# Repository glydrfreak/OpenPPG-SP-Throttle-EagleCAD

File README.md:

# OpenPPG-SP-Throttle-EagleCAD
Eagle CAD files for the OpenPPG Single Prop unit

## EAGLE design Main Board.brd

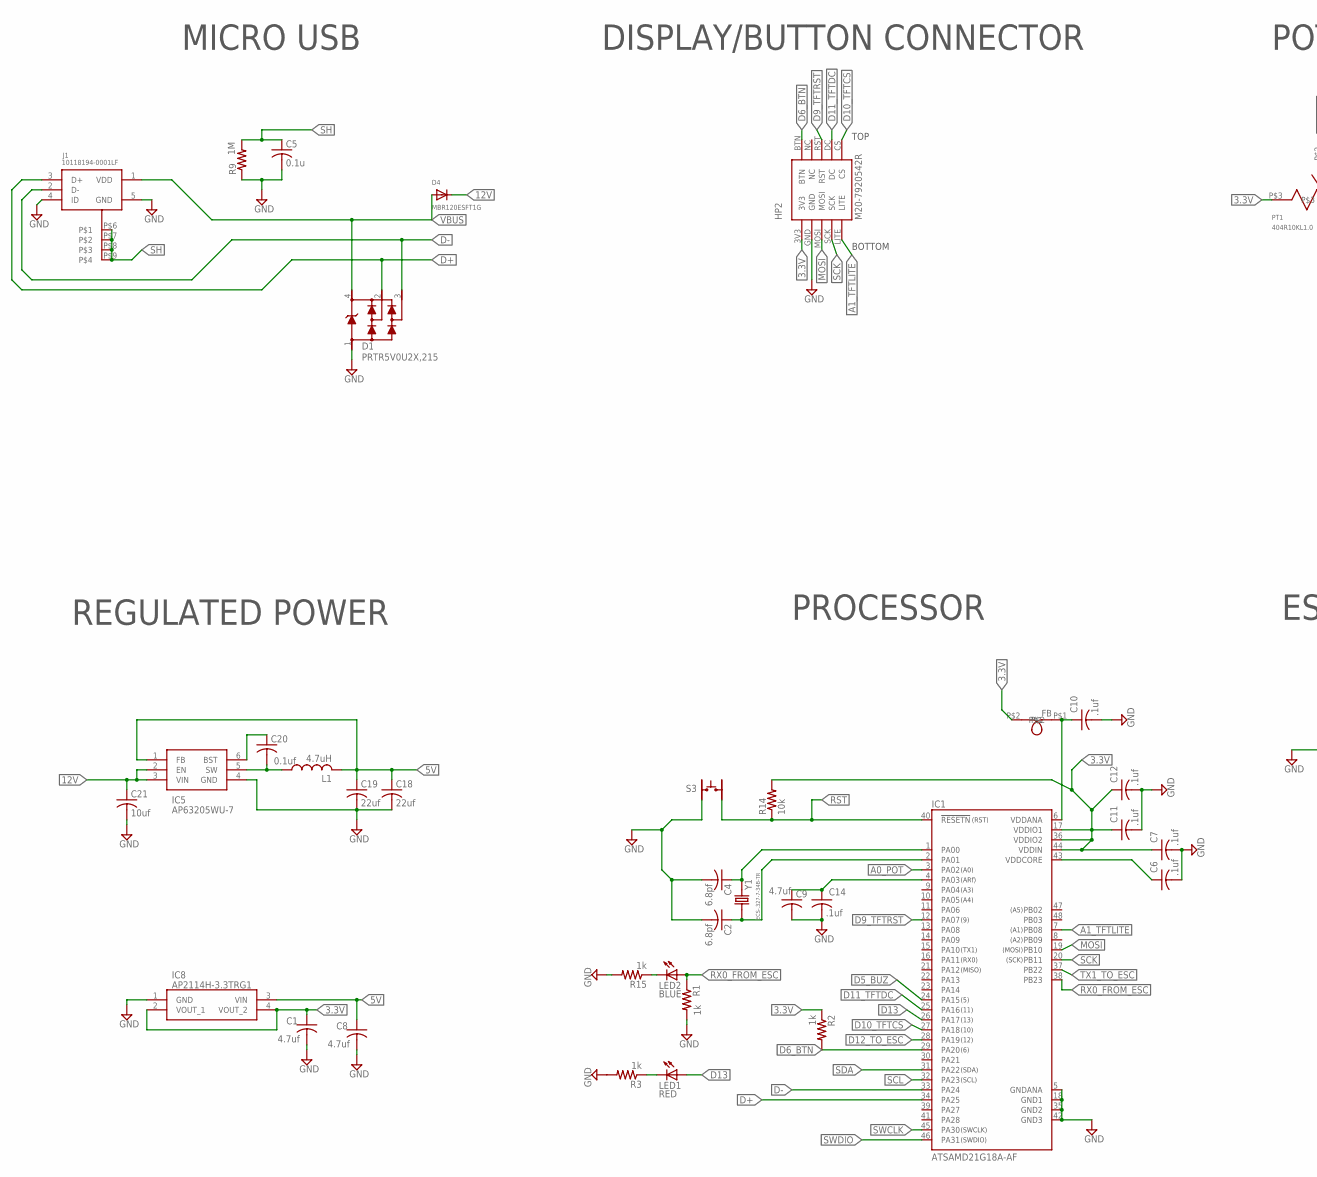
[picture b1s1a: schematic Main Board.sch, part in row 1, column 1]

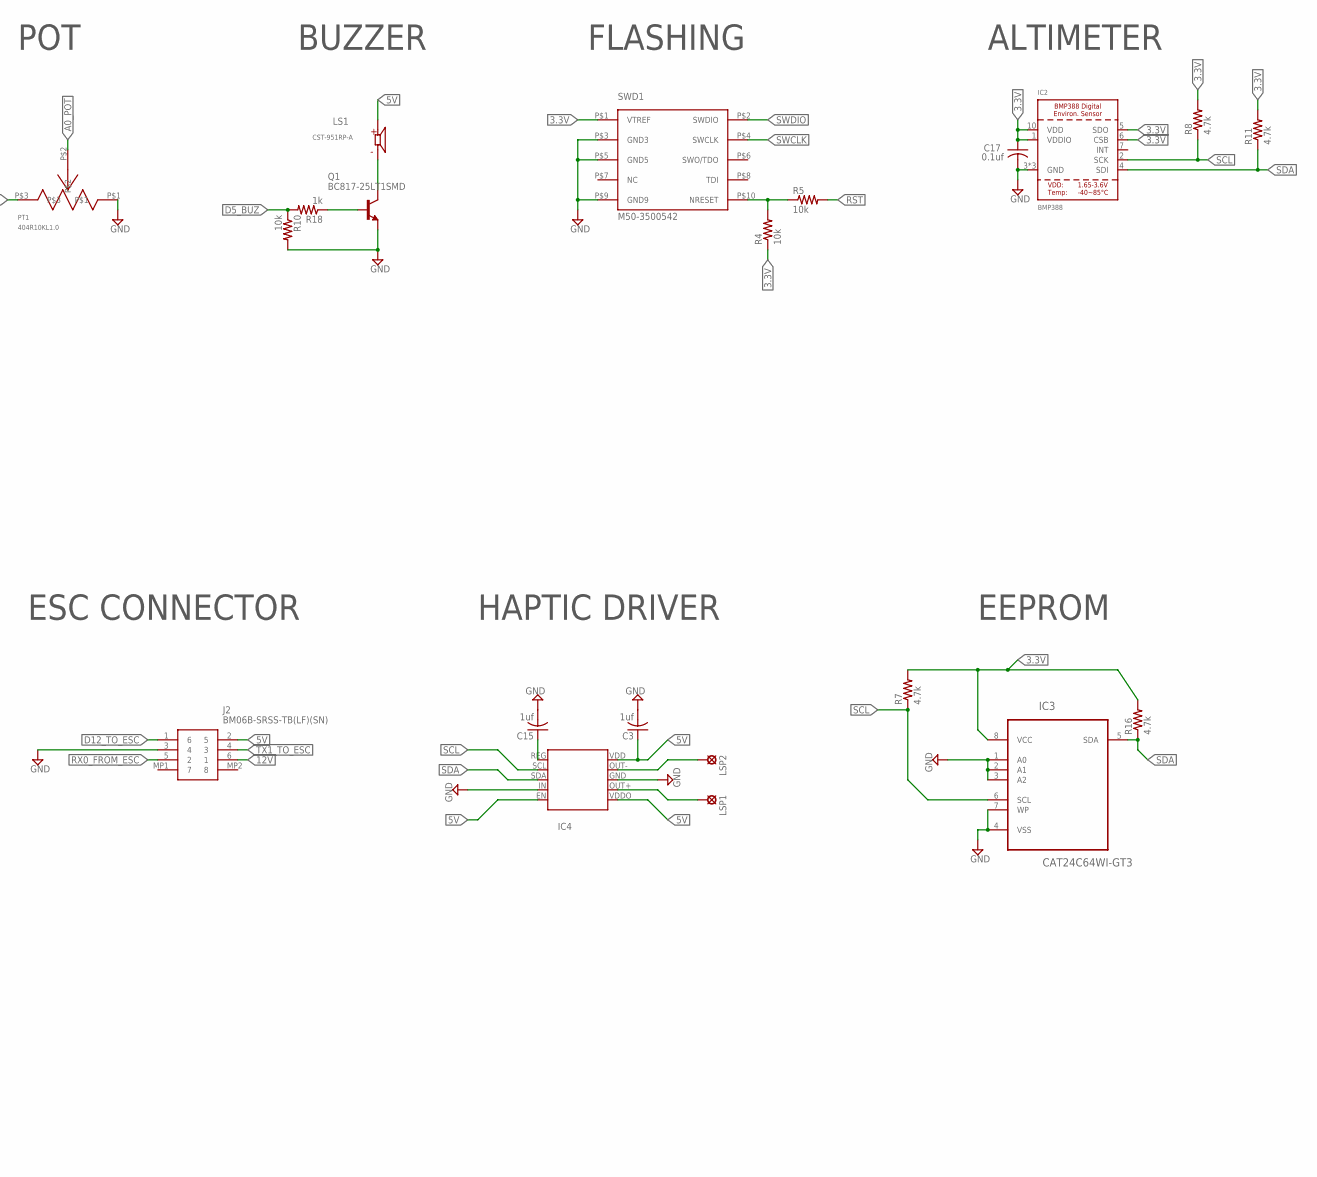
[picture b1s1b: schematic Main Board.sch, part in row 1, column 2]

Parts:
C1, C8, C9: 4.7uf; C0402
C2, C4: 6.8pf; C0402
C3, C15: 1uf; C0402
C5: 0.1u; C0402
C6, C7, C10, C11, C12, C14: .1uf; C0402
C17, C20: 0.1uf; C0402
C18, C19: 22uf; C0603
C21: 10uf; C0805
D1: PRTR5V0U2X,215; SOT143B
D4: MBR120ESFT1G; SOD-123FL
FB: BLM18PG471SN1D; FERRITE_BEAD
HP2: M20-7920542R
IC1: ATSAMD21G18A-AF; QFP50P900X900X120-48N
IC2: BMP388
IC3: CAT24C64WI-GT3; SOIC127P600X175-8N
IC4: DRV2605
IC5: AP63205WU-7; SOT95P280X100-6N
IC8: AP2114H-3.3TRG1; SOT230P700X180-4N
J1: 10118194-0001LF; FRAMATOME_10118194-0001LF
J2: BM06B-SRSS-TB(LF)(SN); BM06BSRSSTBLFSN
L1: 4.7uH; L1812
LED1: RED; CHIP-LED0603
LED2: BLUE; CHIP-LED0603
LS1: CST-951RP-A; CUI_CST-951RP-A
LSP1, LSP2: SE14
PT1: 404R10KL1.0
Q1: BC817-25LT1SMD; SOT23-BEC
R1, R2, R3, R15, R18: 1k; R0402
R4, R5, R10, R14: 10k; R0402
R7, R8, R11, R16: 4.7k; R0402
R9: 1M; R0402
S3: KMR231NG LFS; TATILE_SWITCH
SWD1: M50-3500542
Y1: ECS-.327-7-34B-TR; XTAL_ECS-.327-12.5-34B-C-TR

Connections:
3.3V: C1.1, C7.1, C11.1, C12.1, C17.1, FB.P$2, HP2.3V3, IC1.17 (VDDIO1), IC1.36 (VDDIO2), IC1.44 (VDDIN), IC2.1 (VDDIO), IC2.5 (SDO), IC2.6 (CSB), IC2.10 (VDD), IC3.8 (VCC), IC8.2 (VOUT_1), IC8.4 (VOUT_2), PT1.P$3, R2.1, R4.1, R7.2, R8.2, R11.2, R14.2, R16.2, SWD1.P$1 (VTREF)
5V: C3.1, C8.1, C18.1, C19.1, IC4.EN, IC4.VDD, IC4.VDDO, IC5.1 (FB), IC8.3 (VIN), J2.2 (5), L1.2, LS1.P
12V: C21.1, D4.C, IC5.2 (EN), IC5.3 (VIN), J2.6 (1)
A0_POT: IC1.3 (PA02), PT1.P$2
A1_TFTLITE: HP2.LITE, IC1.7 (PB08)
D5_BUZ: IC1.24 (PA15), R10.1, R18.2
D6_BTN: HP2.BTN, IC1.29 (PA20), R2.2
D9_TFTRST: HP2.RST, IC1.12 (PA07)
D10_TFTCS: HP2.CS, IC1.27 (PA18)
D11_TFTDC: HP2.DC, IC1.25 (PA16)
D12_TO_ESC: IC1.28 (PA19), J2.1 (6)
D13: IC1.26 (PA17), LED1.A
D+: D1.2, IC1.34 (PA25), J1.3 (D+)
D-: D1.3, IC1.33 (PA24), J1.2 (D-)
GND: C1.2, C2.2, C3.2, C4.2, C5.2, C6.2, C7.2, C8.2, C9.2, C10.2, C11.2, C12.2, C14.2, C15.2, C17.2, C18.2, C19.2, C21.2, D1.1, HP2.GND, IC1.5 (GNDANA), IC1.18 (GND1), IC1.35 (GND2), IC1.42 (GND3), IC2.3 (GND), IC2.8 (GND), IC2.9 (GND), IC3.1 (A0), IC3.2 (A1), IC3.3 (A2), IC3.4 (VSS), IC3.7 (WP), IC4.GND, IC4.IN, IC5.4 (GND), IC8.1 (GND), J1.4 (ID), J1.5 (GND), J2.3 (4), PT1.P$1, Q1.E, R1.2, R3.2, R9.1, R10.2, R15.2, S3.P$3, SWD1.P$3 (GND3), SWD1.P$5 (GND5), SWD1.P$9 (GND9)
MOSI: HP2.MOSI, IC1.19 (PB10)
unnamed: C6.1, IC1.43 (VDDCORE)
unnamed: LED1.C, R3.1
unnamed: C4.1, IC1.1 (PA00), Y1.2
unnamed: C2.1, IC1.2 (PA01), Y1.1
unnamed: C10.1, FB.P$1, IC1.6 (VDDANA)
unnamed: R4.2, R5.1, SWD1.P$10 (NRESET)
unnamed: C20.2, IC5.5 (SW), L1.1
unnamed: C20.1, IC5.6 (BST)
unnamed: LED2.C, R15.1
unnamed: IC4.OUT-, LSP2.MP
unnamed: C9.1, C14.1, IC1.4 (PA03)
unnamed: Q1.B, R18.1
unnamed: LS1.M, Q1.C
unnamed: C15.1, IC4.REG
unnamed: IC4.OUT+, LSP1.MP
RST: IC1.40 (!RESETN), R5.2, R14.1, S3.P$4
RX0_FROM_ESC: IC1.38 (PB23), J2.5 (2), LED2.A, R1.1
SCK: HP2.SCK, IC1.20 (PB11)
SCL: IC1.32 (PA23), IC2.2 (SCK), IC3.6 (SCL), IC4.SCL, R7.1, R8.1
SDA: IC1.31 (PA22), IC2.4 (SDI), IC3.5 (SDA), IC4.SDA, R11.1, R16.1
SH: C5.1, J1.P$6, J1.P$7, J1.P$8, J1.P$9, R9.2
SWCLK: IC1.45 (PA30), SWD1.P$4 (SWCLK)
SWDIO: IC1.46 (PA31), SWD1.P$2 (SWDIO)
TX1_TO_ESC: IC1.37 (PB22), J2.4 (3)
VBUS: D1.4, D4.A, J1.1 (VDD)

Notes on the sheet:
POT
BUZZER
DISPLAY/BUTTON CONNECTOR
EEPROM
HAPTIC DRIVER
FLASHING
MICRO USB
PROCESSOR
ESC CONNECTOR
REGULATED POWER
ALTIMETER

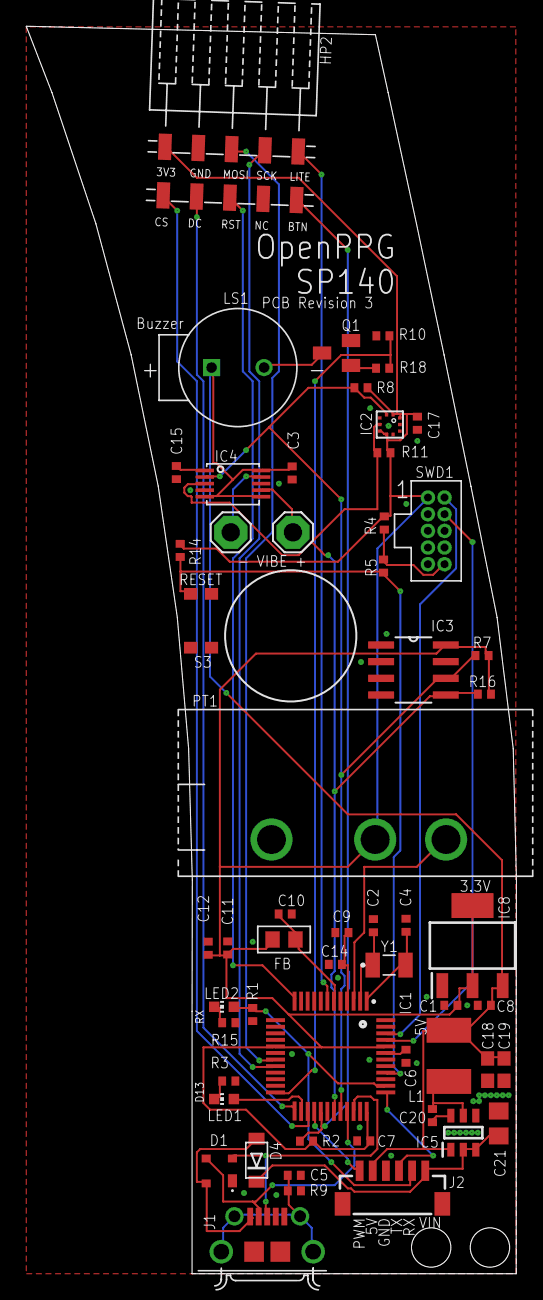
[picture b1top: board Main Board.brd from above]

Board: 2 copper layers, 37.3 x 95.0 mm, 56 parts (0 on the bottom side), 41 nets.

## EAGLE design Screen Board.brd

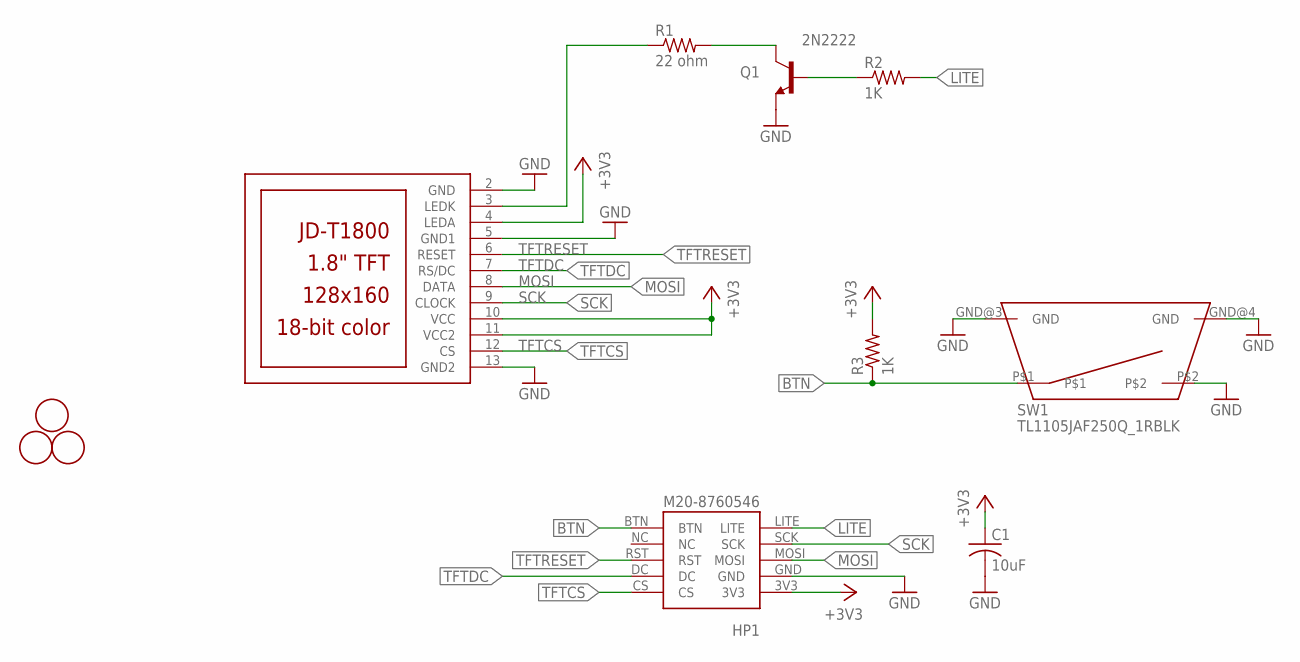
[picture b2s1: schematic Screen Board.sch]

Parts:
C1: 10uF; C0805K
HP1: M20-8760546
Q1: 2N2222; SOT23-BEC
R1: 22 ohm; R0805
R2, R3: 1K; R0805
SW1: TL1105JAF250Q_1RBLK
U$1: JD-T1800
U$3, U$4, U$5: FIDUCIAL; FIDUCIAL_1MM

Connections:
+3V3: C1.1, HP1.3V3, R3.2, U$1.4 (LEDA), U$1.10 (VCC), U$1.11 (VCC2)
BTN: HP1.BTN, R3.1, SW1.P$1
GND: C1.2, HP1.GND, Q1.E, SW1.GND@3 (GND), SW1.GND@4 (GND), SW1.P$2, U$1.2 (GND), U$1.5 (GND1), U$1.13 (GND2)
LITE: HP1.LITE, R2.2
MOSI: HP1.MOSI, U$1.8 (DATA)
unnamed: Q1.B, R2.1
unnamed: R1.1, U$1.3 (LEDK)
unnamed: Q1.C, R1.2
SCK: HP1.SCK, U$1.9 (CLOCK)
TFTCS: HP1.CS, U$1.12 (CS)
TFTDC: HP1.DC, U$1.7 (RS/DC)
TFTRESET: HP1.RST, U$1.6 (RESET)

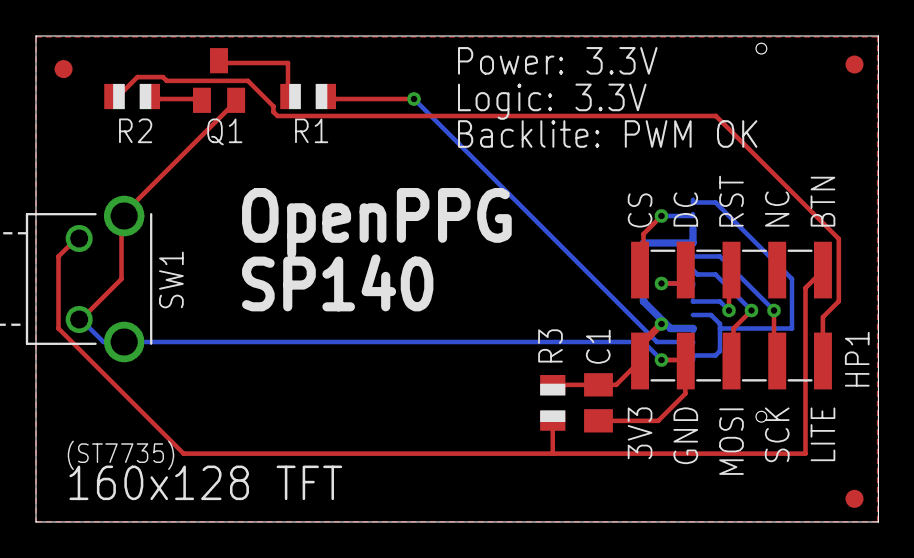
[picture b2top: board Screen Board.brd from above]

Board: 2 copper layers, 46.8 x 27.0 mm, 11 parts (1 on the bottom side), 12 nets.

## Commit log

2019-08-20 6 pin SH connector instead of two 4 pin SH connectors
2019-08-27 Switching regulator to reduce heat, and added ground planes
2019-08-27 Board Identifier SP140
2019-09-19 fixed C21 tplace silkscreen, fixed esc connector silkscreen spacing, fixed too big 0402 cap footprints
2019-09-19 C21 tplace silkscreen, fixed esc connector silkscreen spacing, fixed too big 0402 cap footprints
2019-10-07 Rx and Tx to pin 37 and 38; Shifted location of JST; Added holes for zip tie
2019-10-07 Silkscreen fixes and added PCB revision label
2019-10-08 Location of zip tie holes
2019-11-14 adjusted location of zip tie holes
